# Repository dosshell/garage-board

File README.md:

# garage-board
Replacement card for my garage port

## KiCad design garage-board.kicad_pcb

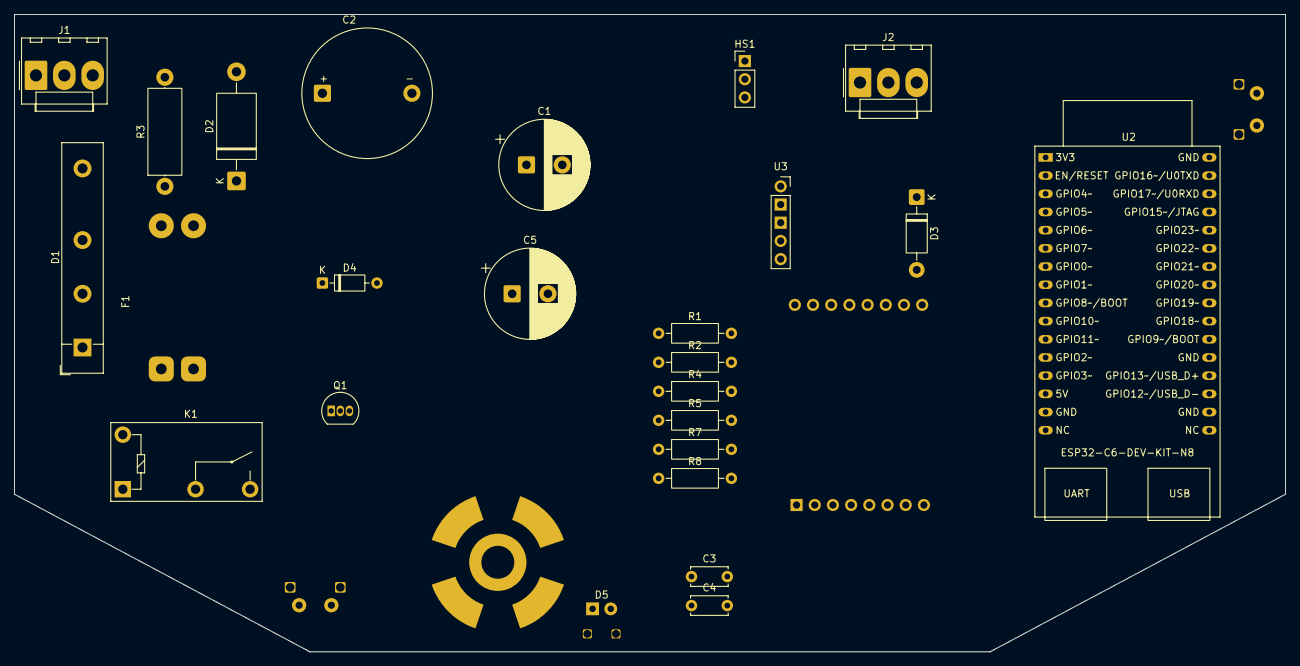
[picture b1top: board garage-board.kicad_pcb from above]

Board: 2 copper layers, 177.5 x 89.0 mm, 29 parts (0 on the bottom side), 26 nets, no tracks yet.

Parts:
C1, C5: 470uF 63V 105C ESR; CP_Radial_D12.5mm_P5.00mm
C2: 4700uF 63V 105C ESR; CP_Radial_D25.0mm_P12.50mm
C3, C4: 100nF; C_Disc_D5.0mm_W2.5mm_P5.00mm
D1: B125 C7000-4000; Diode_Bridge_32.0x5.6x17.0mm_P10.0mm_P7.5mm
D2: 1.5KE39A; D_DO-201AE_P15.24mm_Horizontal
D3: 1N4007; D_DO-41_SOD81_P10.16mm_Horizontal
D4: 1N4148; D_DO-35_SOD27_P7.62mm_Horizontal
D5: Red; LED_D5.0mm_Horizontal
F1: T6.3A; Fuseholder_5x20mm_Lateral_P20.00x5.00mm
HS1: HAL503; PinHeader_1x03_P2.54mm_Vertical
J1: 24VAC; Molex_KK-396_A-41791-0003_1x03_P3.96mm_Vertical
J2: Motor; Molex_KK-396_A-41791-0003_1x03_P3.96mm_Vertical
K1: G5Q-1A; Relay_SPST_Omron-G5Q-1A
LA1: Lamp; lamp
Q1: BC547; TO-92_Inline
R1, R4, R7: 4.7k; R_Axial_DIN0207_L6.3mm_D2.5mm_P10.16mm_Horizontal
R2: 10k; R_Axial_DIN0207_L6.3mm_D2.5mm_P10.16mm_Horizontal
R3: 10k (0.5W); R_Axial_DIN0414_L11.9mm_D4.5mm_P15.24mm_Horizontal
R5: 1k; R_Axial_DIN0207_L6.3mm_D2.5mm_P10.16mm_Horizontal
R8: 680; R_Axial_DIN0207_L6.3mm_D2.5mm_P10.16mm_Horizontal
SW2, SW3: SW_Push; Switch
U1: Pololu-2993; Pololu Motor Driver 2993
U2: ESP32-C6-DEV-KIT-N8; ESP32-C6-DevKitC-1
U3: Pololu-4892; Pololu 4892

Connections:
+3V3: R1.1, U1.7 (VCC), U2.1 (3V3)
+5V: C4.2, HS1.2 (+), U2.14 (5V), U3.1 (VOUT)
GND: C1.2, C2.2, C3.2, C4.1, C5.2, D1.1 (-), D2.2 (A2), D5.1 (K), HS1.3 (GND), J2.3, Q1.3 (E), R3.1, R4.2, SW2.2, SW3.2, U1.1 (GND), U1.12 (GND), U2.15 (GND), U2.18 (GND), U2.21 (GND), U2.32 (GND), U3.2 (GND), U3.3 (GND)
unnamed: C2.1, D1.4 (+), D2.1 (A1), D3.2 (A), R3.2, U1.9 (VIN)
unnamed: C5.1, D3.1 (K), R8.2, U3.4 (VIN)
unnamed: D4.2 (A), K1.5, Q1.1 (C)
unnamed: D4.1 (K), K1.1, R8.1
unnamed: D5.2 (A), R5.2
unnamed: HS1.1 (A), R1.2, R2.1
unnamed: F1.2, J1.1
unnamed: D1.2, J1.3, K1.3
unnamed: J2.1, U1.11 (OUTB)
unnamed: J2.2, U1.10 (OUTA)
unnamed: D1.3, F1.1, LA1.2 (+)
unnamed: K1.2, LA1.1 (-)
unnamed: Q1.2 (B), R7.1
unnamed: U1.6 (CS), U2.12 (GPIO2)
unnamed: U1.3 (PWMA), U2.25 (GPIO20)
unnamed: U1.2 (PWMB), U2.26 (GPIO21)
unnamed: U1.5 (~FLT), U2.23 (GPIO18)
unnamed: R4.1, U1.4 (~SLP), U2.24 (GPIO19)
unnamed: R7.2, U2.6 (GPIO7)
unnamed: R5.1, U2.10 (GPIO10)
unnamed: C3.1, R2.2, U2.11 (GPIO11)
unnamed: SW2.1, U2.27 (GPIO22)
unnamed: SW3.1, U2.28 (GPIO23)
